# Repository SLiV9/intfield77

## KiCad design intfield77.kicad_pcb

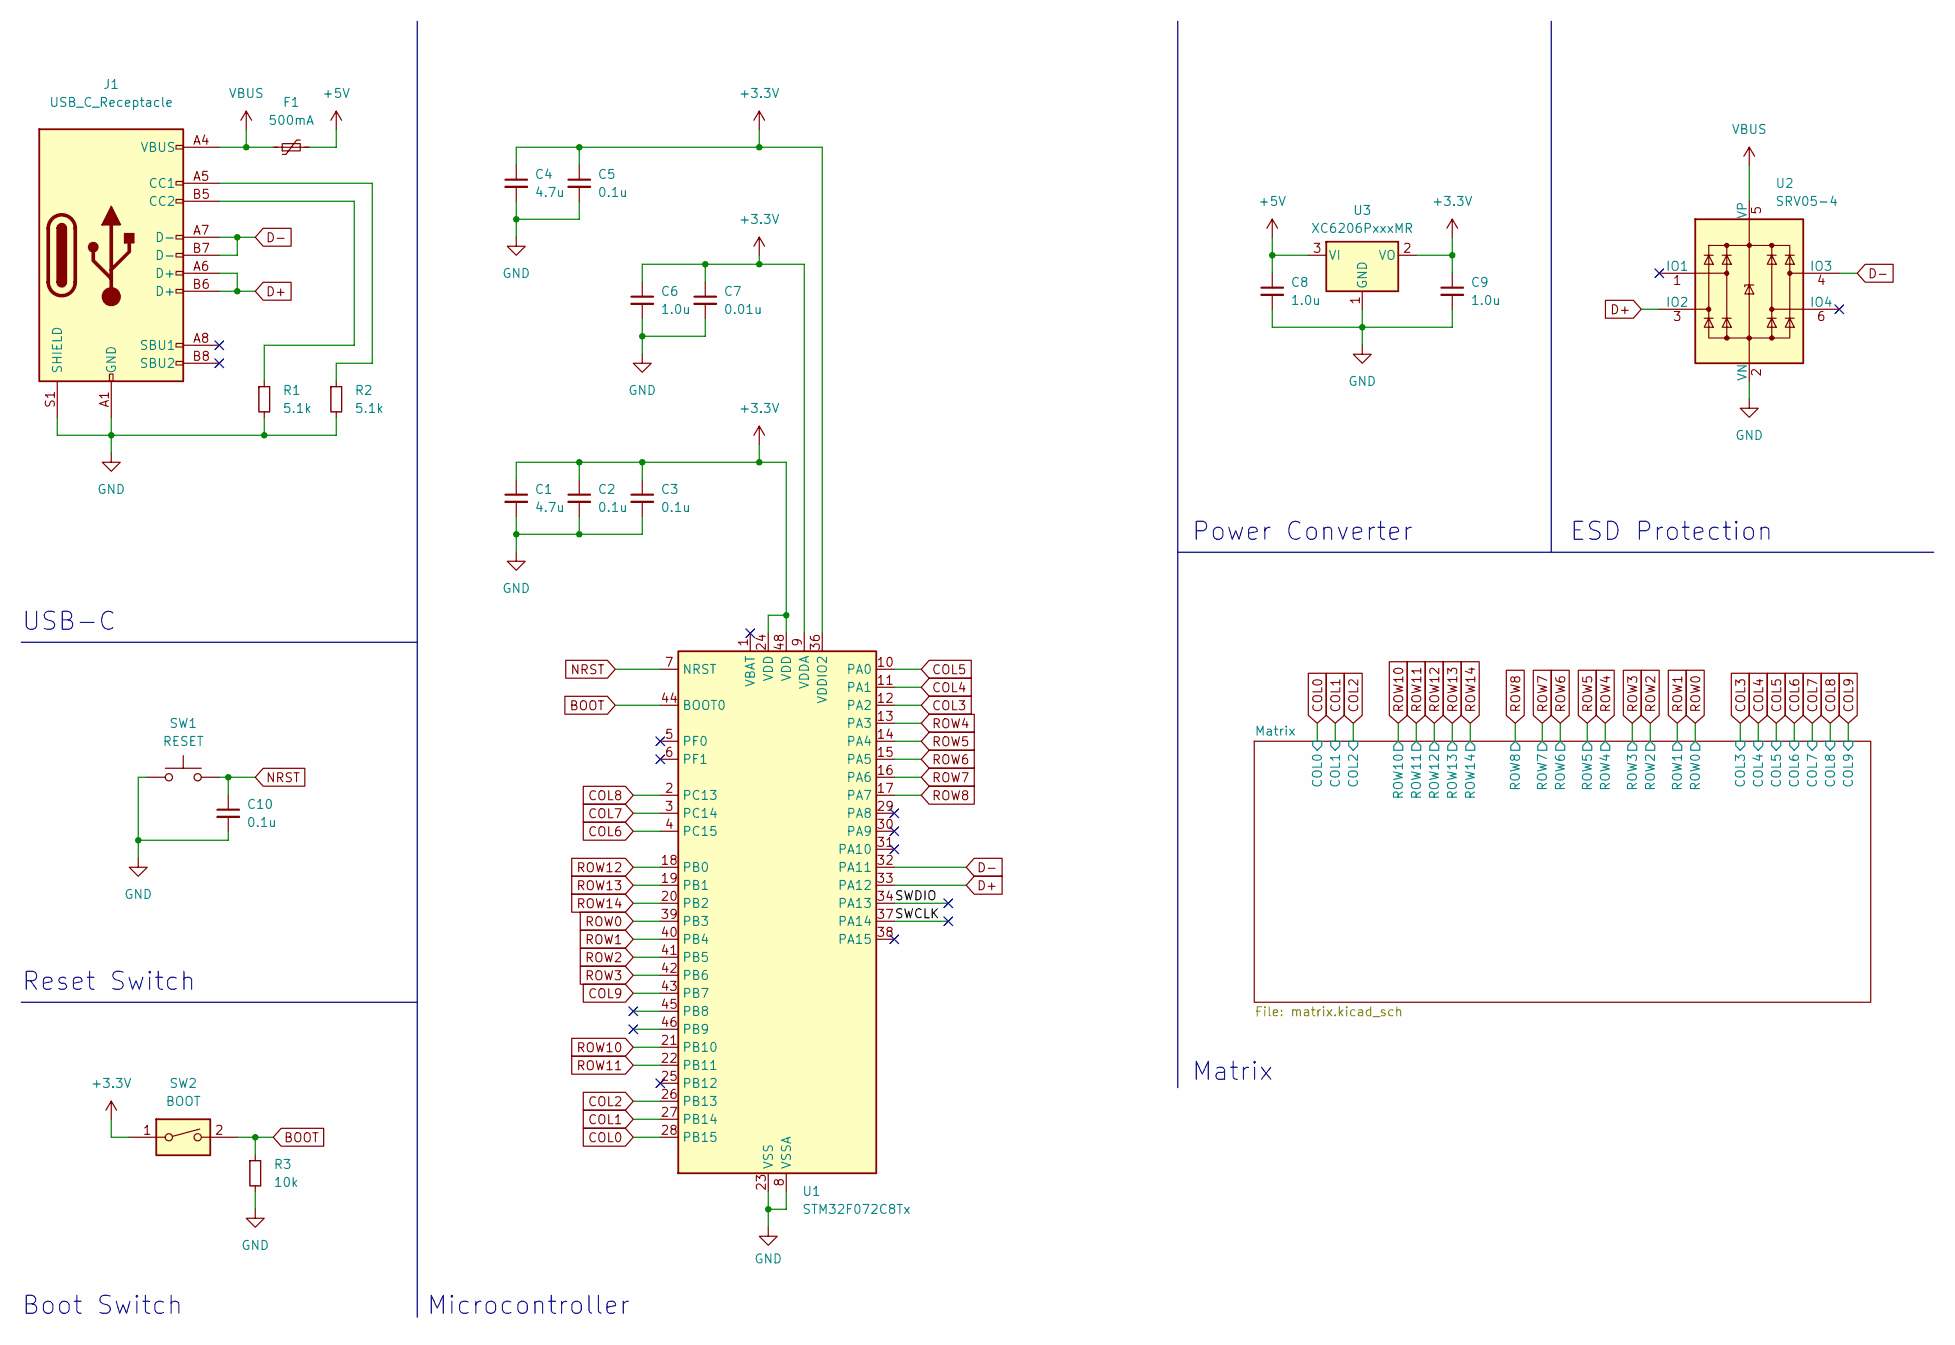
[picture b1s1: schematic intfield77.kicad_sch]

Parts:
C1, C4: 4.7u; C_0805_2012Metric
C2, C3, C5, C10: 0.1u; C_0805_2012Metric
C6, C8, C9: 1.0u; C_0805_2012Metric
C7: 0.01u; C_0805_2012Metric
F1: 500mA; Fuse_1206_3216Metric
J1: USB_C_Receptacle; USB_C_Receptacle_HRO_TYPE-C-31-M-12
R1, R2: 5.1k; R_0805_2012Metric
R3: 10k; R_0805_2012Metric
SW1: RESET; SW_SPST_SKQG_WithStem
SW2: BOOT; SW_DIP_SPSTx01_Slide_9.78x4.72mm_W8.61mm_P2.54mm
U1: STM32F072C8Tx; LQFP-48_7x7mm_P0.5mm
U2: SRV05-4; SOT-23-6-routable
U3: XC6206PxxxMR; SOT-23-3

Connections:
+3.3V: C1.1, C2.1, C3.1, C4.1, C5.1, C6.1, C7.1, C9.1, SW2.1, U1.9 (VDDA), U1.24 (VDD), U1.36 (VDDIO2), U1.48 (VDD), U3.2 (VO)
+5V: C8.1, F1.2, U3.3 (VI)
/SWCLK: U1.37 (PA14)
/SWDIO: U1.34 (PA13)
BOOT: R3.1, SW2.2, U1.44 (BOOT0)
COL0: U1.28 (PB15); also elsewhere on the board
COL1: U1.27 (PB14); also elsewhere on the board
COL2: U1.26 (PB13); also elsewhere on the board
COL3: U1.12 (PA2); also elsewhere on the board
COL4: U1.11 (PA1); also elsewhere on the board
COL5: U1.10 (PA0); also elsewhere on the board
COL6: U1.4 (PC15); also elsewhere on the board
COL7: U1.3 (PC14); also elsewhere on the board
COL8: U1.2 (PC13); also elsewhere on the board
COL9: U1.43 (PB7); also elsewhere on the board
D+: J1.A6 (D+), J1.B6 (D+), U1.33 (PA12), U2.3 (IO2)
D-: J1.A7 (D-), J1.B7 (D-), U1.32 (PA11), U2.4 (IO3)
GND: C1.2, C2.2, C3.2, C4.2, C5.2, C6.2, C7.2, C8.2, C9.2, C10.2, J1.A1 (GND), J1.A12 (GND), J1.B1 (GND), J1.B12 (GND), J1.S1 (SHIELD), R1.2, R2.2, R3.2, SW1.1, U1.8 (VSSA), U1.23 (VSS), U1.35 (VSS), U1.47 (VSS), U2.2 (VN), U3.1 (GND)
NRST: C10.1, SW1.2, U1.7 (NRST)
unnamed: J1.A5 (CC1), R2.1
unnamed: J1.B5 (CC2), R1.1
ROW0: U1.39 (PB3); also elsewhere on the board
ROW1: U1.40 (PB4); also elsewhere on the board
ROW2: U1.41 (PB5); also elsewhere on the board
ROW3: U1.42 (PB6); also elsewhere on the board
ROW4: U1.13 (PA3); also elsewhere on the board
ROW5: U1.14 (PA4); also elsewhere on the board
ROW6: U1.15 (PA5); also elsewhere on the board
ROW7: U1.16 (PA6); also elsewhere on the board
ROW8: U1.17 (PA7); also elsewhere on the board
ROW10: U1.21 (PB10); also elsewhere on the board
ROW11: U1.22 (PB11); also elsewhere on the board
ROW12: U1.18 (PB0); also elsewhere on the board
ROW13: U1.19 (PB1); also elsewhere on the board
ROW14: U1.20 (PB2); also elsewhere on the board
VBUS: F1.1, J1.A4 (VBUS), J1.A9 (VBUS), J1.B4 (VBUS), J1.B9 (VBUS), U2.5 (VP)

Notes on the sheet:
Boot Switch
Power Converter
Matrix
Reset Switch
USB-C
Microcontroller
ESD Protection

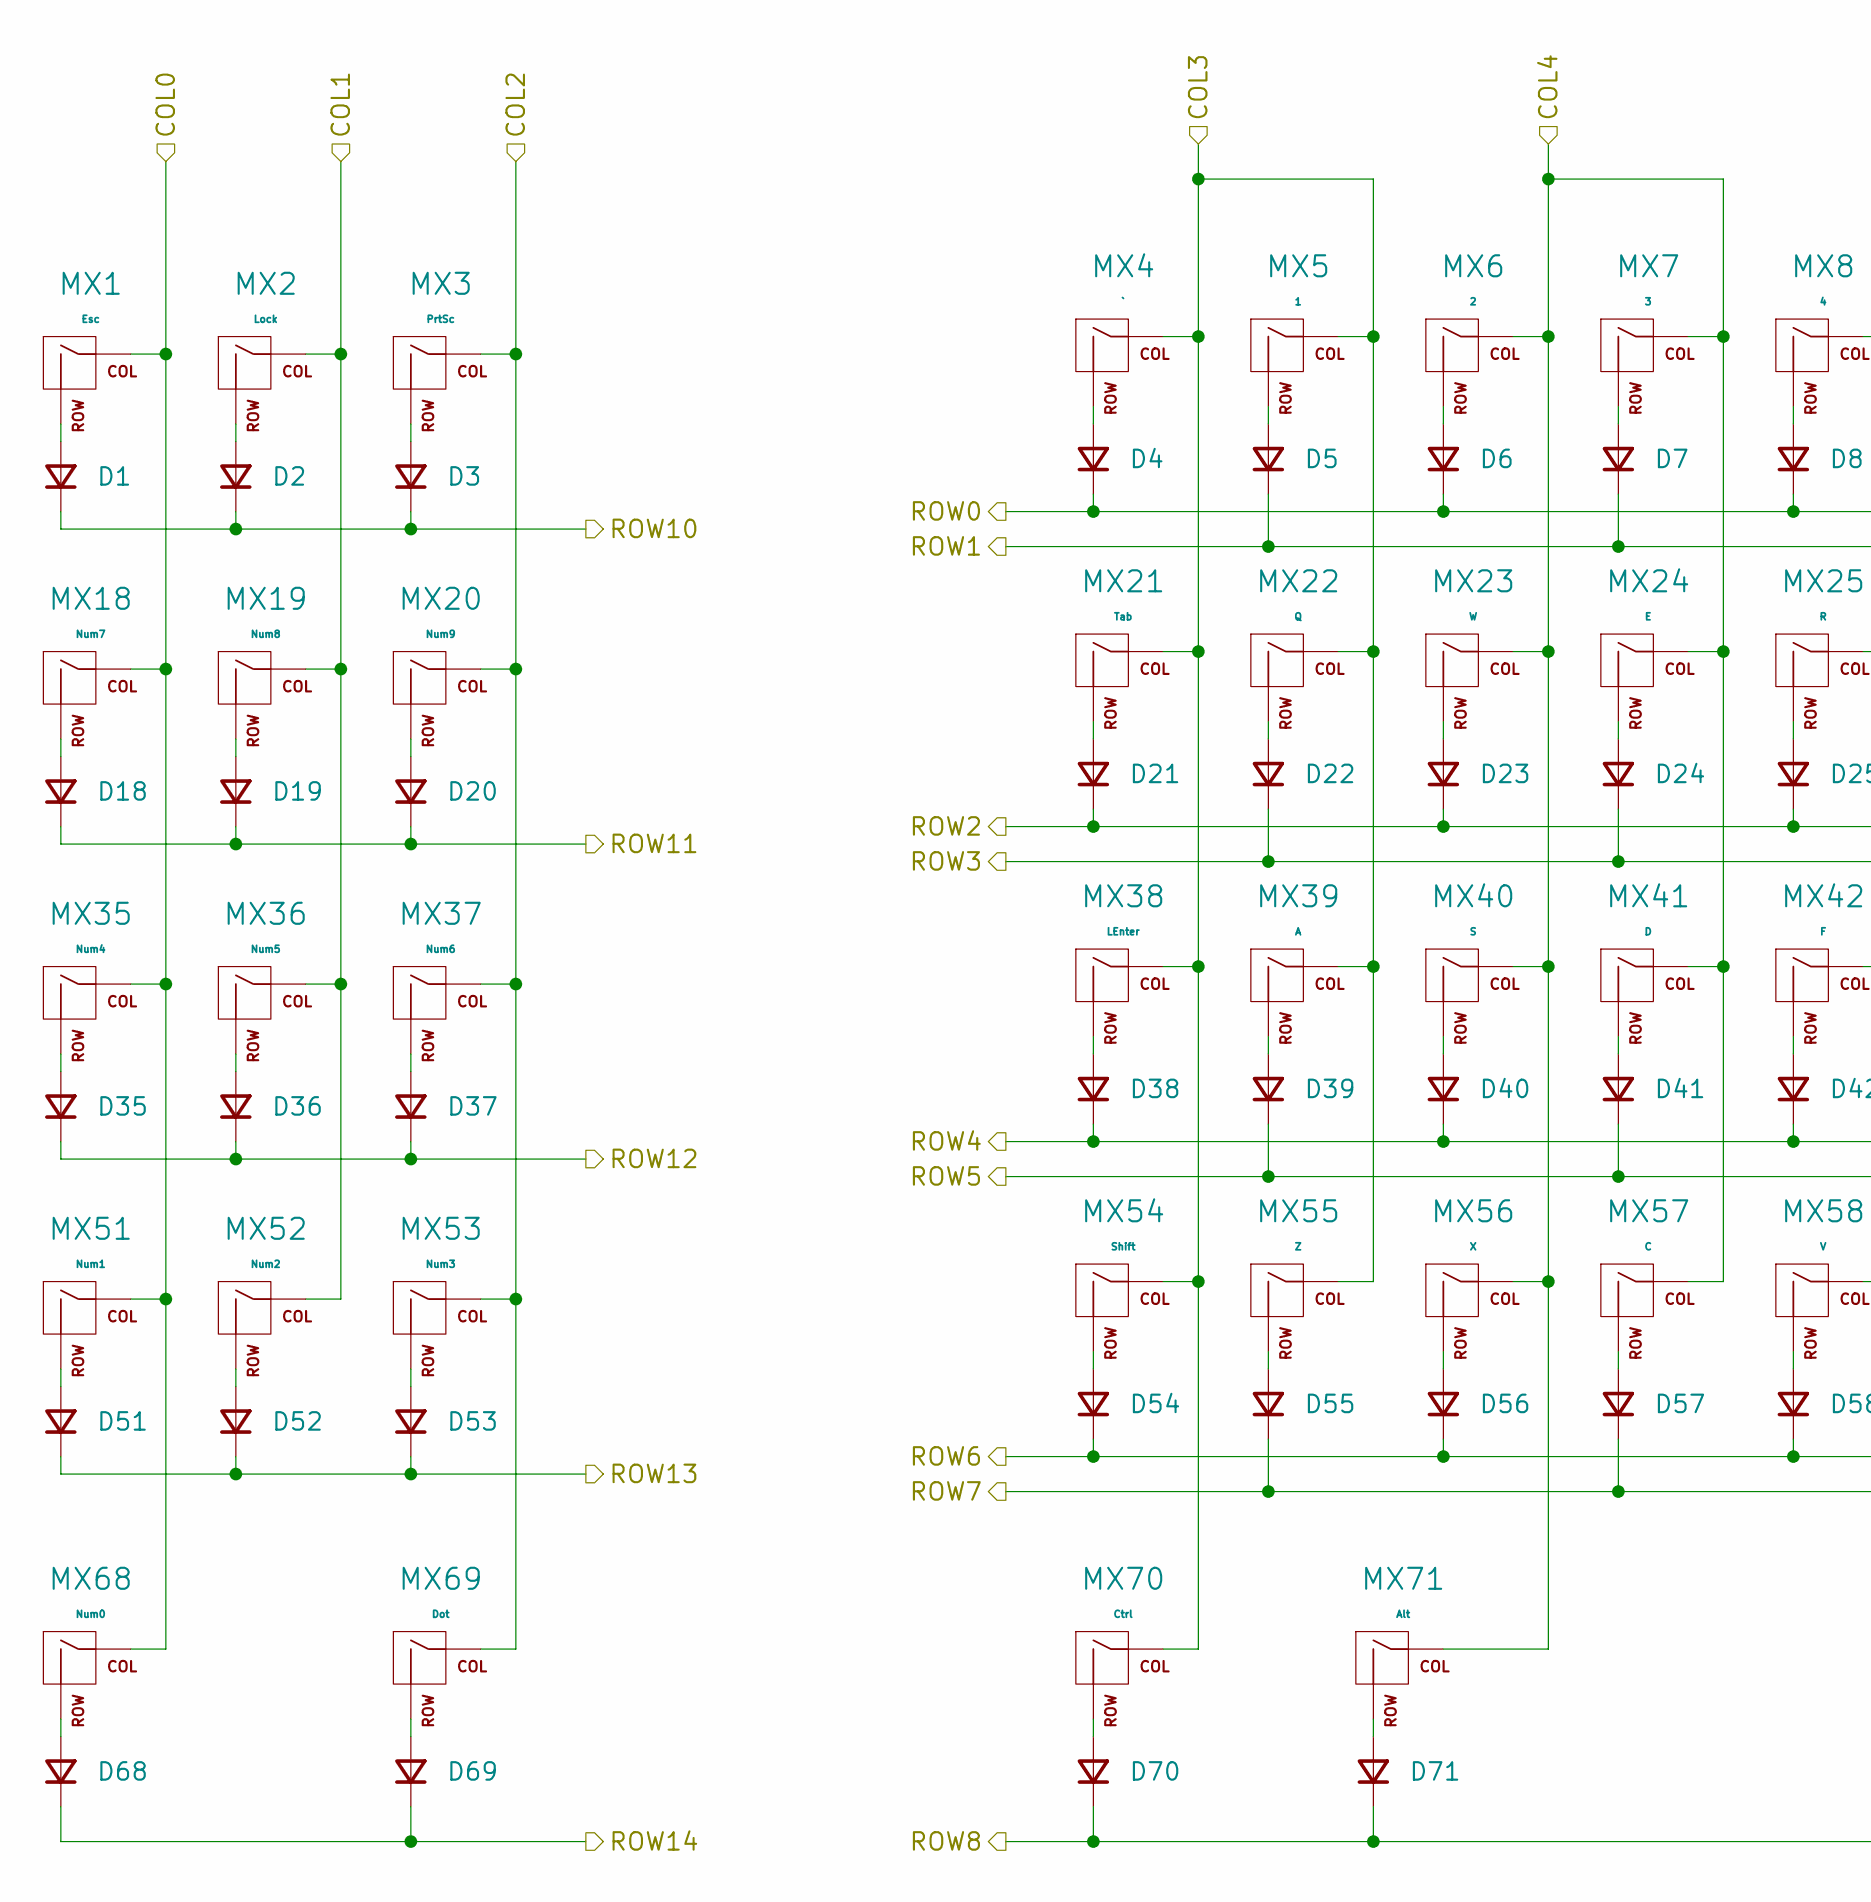
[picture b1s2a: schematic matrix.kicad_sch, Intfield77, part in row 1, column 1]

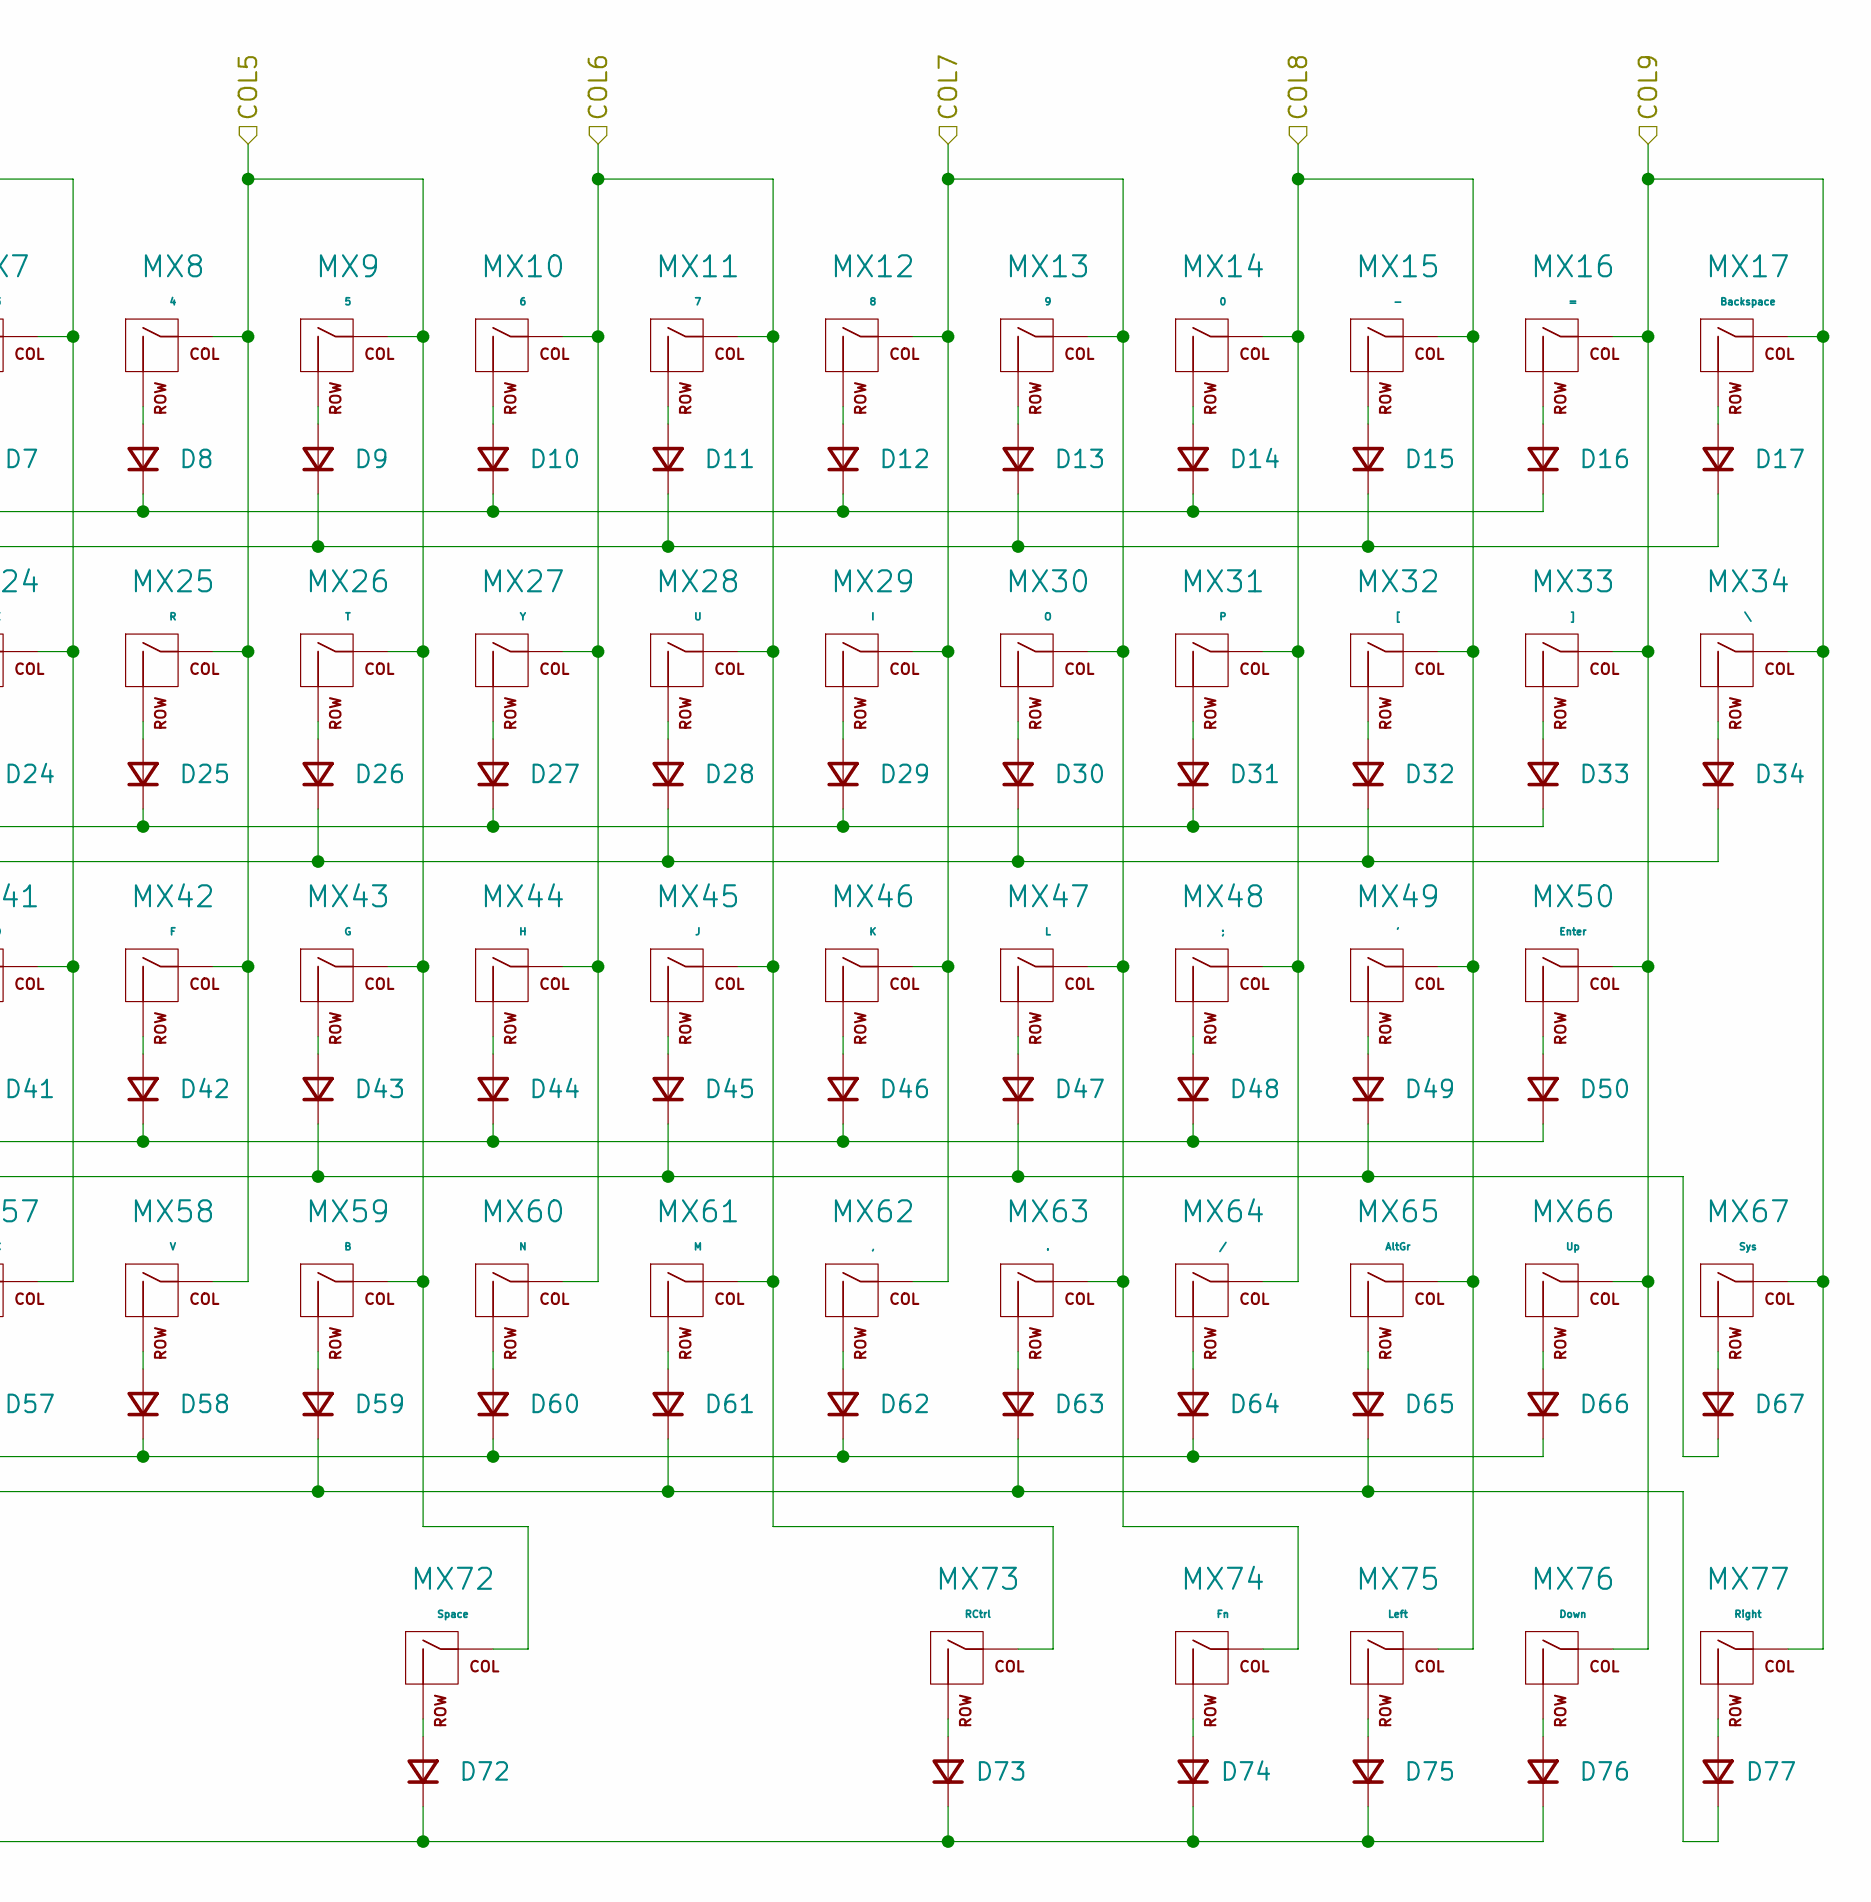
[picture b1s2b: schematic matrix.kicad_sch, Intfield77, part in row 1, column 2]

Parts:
D1, D2, D3, D4, D5, D6, D7, D8, D9, D10, D11, D12, D13, D14, D15, D16, D17, D18, D19, D20, D21, D22, D23, D24, D25, D26, D27, D28, D29, D30, D31, D32, D33, D34, D35, D36, D37, D38, D39, D40, D41, D42, D43, D44, D45, D46, D47, D48, D49, D50, D51, D52, D53, D54, D55, D56, D57, D58, D59, D60, D61, D62, D63, D64, D65, D66, D67, D68, D69, D70, D71, D72, D73, D74, D75, D76, D77: D_SOD-123
MX1: Esc; MXOnly-1U-NoLED
MX2: Lock; MXOnly-1U-NoLED
MX3: PrtSc; MXOnly-1U-NoLED
MX4: `; MXOnly-1U-NoLED
MX5: 1; MXOnly-1U-NoLED
MX6: 2; MXOnly-1U-NoLED
MX7: 3; MXOnly-1U-NoLED
MX8: 4; MXOnly-1U-NoLED
MX9: 5; MXOnly-1U-NoLED
MX10: 6; MXOnly-1U-NoLED
MX11: 7; MXOnly-1U-NoLED
MX12: 8; MXOnly-1U-NoLED
MX13: 9; MXOnly-1U-NoLED
MX14: 0; MXOnly-1U-NoLED
MX15: -; MXOnly-1U-NoLED
MX16: =; MXOnly-1U-NoLED
MX17: Backspace; MXOnly-2U-NoLED
MX18: Num7; MXOnly-1U-NoLED
MX19: Num8; MXOnly-1U-NoLED
MX20: Num9; MXOnly-1U-NoLED
MX21: Tab; MXOnly-1.5U-NoLED
MX22: Q; MXOnly-1U-NoLED
MX23: W; MXOnly-1U-NoLED
MX24: E; MXOnly-1U-NoLED
MX25: R; MXOnly-1U-NoLED
MX26: T; MXOnly-1U-NoLED
MX27: Y; MXOnly-1U-NoLED
MX28: U; MXOnly-1U-NoLED
MX29: I; MXOnly-1U-NoLED
MX30: O; MXOnly-1U-NoLED
MX31: P; MXOnly-1U-NoLED
MX32: [; MXOnly-1U-NoLED
MX33: ]; MXOnly-1U-NoLED
MX34: \; MXOnly-1.5U-NoLED
MX35: Num4; MXOnly-1U-NoLED
MX36: Num5; MXOnly-1U-NoLED
MX37: Num6; MXOnly-1U-NoLED
MX38: LEnter; MXOnly-1.75U-NoLED
MX39: A; MXOnly-1U-NoLED
MX40: S; MXOnly-1U-NoLED
MX41: D; MXOnly-1U-NoLED
MX42: F; MXOnly-1U-NoLED
MX43: G; MXOnly-1U-NoLED
MX44: H; MXOnly-1U-NoLED
MX45: J; MXOnly-1U-NoLED
MX46: K; MXOnly-1U-NoLED
MX47: L; MXOnly-1U-NoLED
MX48: ;; MXOnly-1U-NoLED
MX49: '; MXOnly-1U-NoLED
MX50: Enter; MXOnly-2.25U-NoLED
MX51: Num1; MXOnly-1U-NoLED
MX52: Num2; MXOnly-1U-NoLED
MX53: Num3; MXOnly-1U-NoLED
MX54: Shift; MXOnly-2U-NoLED
MX55: Z; MXOnly-1U-NoLED
MX56: X; MXOnly-1U-NoLED
MX57: C; MXOnly-1U-NoLED
MX58: V; MXOnly-1U-NoLED
MX59: B; MXOnly-1U-NoLED
MX60: N; MXOnly-1U-NoLED
MX61: M; MXOnly-1U-NoLED
MX62: ,; MXOnly-1U-NoLED
MX63: .; MXOnly-1U-NoLED
MX64: /; MXOnly-1U-NoLED
MX65: AltGr; MXOnly-1U-NoLED
MX66: Up; MXOnly-1U-NoLED
MX67: Sys; MXOnly-1U-NoLED
MX68: Num0; MXOnly-2U-NoLED
MX69: Dot; MXOnly-1U-NoLED
MX70: Ctrl; MXOnly-1.25U-NoLED
MX71: Alt; MXOnly-1.25U-NoLED
MX72: Space; MXOnly-7U-NoLED
MX73: RCtrl; MXOnly-1.25U-NoLED
MX74: Fn; MXOnly-1.25U-NoLED
MX75: Left; MXOnly-1U-NoLED
MX76: Down; MXOnly-1U-NoLED
MX77: Right; MXOnly-1U-NoLED

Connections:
COL0: MX1.1 (COL), MX18.1 (COL), MX35.1 (COL), MX51.1 (COL), MX68.1 (COL); also elsewhere on the board
COL1: MX2.1 (COL), MX19.1 (COL), MX36.1 (COL), MX52.1 (COL); also elsewhere on the board
COL2: MX3.1 (COL), MX20.1 (COL), MX37.1 (COL), MX53.1 (COL), MX69.1 (COL); also elsewhere on the board
COL3: MX4.1 (COL), MX5.1 (COL), MX21.1 (COL), MX22.1 (COL), MX38.1 (COL), MX39.1 (COL), MX54.1 (COL), MX55.1 (COL), MX70.1 (COL); also elsewhere on the board
COL4: MX6.1 (COL), MX7.1 (COL), MX23.1 (COL), MX24.1 (COL), MX40.1 (COL), MX41.1 (COL), MX56.1 (COL), MX57.1 (COL), MX71.1 (COL); also elsewhere on the board
COL5: MX8.1 (COL), MX9.1 (COL), MX25.1 (COL), MX26.1 (COL), MX42.1 (COL), MX43.1 (COL), MX58.1 (COL), MX59.1 (COL), MX72.1 (COL); also elsewhere on the board
COL6: MX10.1 (COL), MX11.1 (COL), MX27.1 (COL), MX28.1 (COL), MX44.1 (COL), MX45.1 (COL), MX60.1 (COL), MX61.1 (COL), MX73.1 (COL); also elsewhere on the board
COL7: MX12.1 (COL), MX13.1 (COL), MX29.1 (COL), MX30.1 (COL), MX46.1 (COL), MX47.1 (COL), MX62.1 (COL), MX63.1 (COL), MX74.1 (COL); also elsewhere on the board
COL8: MX14.1 (COL), MX15.1 (COL), MX31.1 (COL), MX32.1 (COL), MX48.1 (COL), MX49.1 (COL), MX64.1 (COL), MX65.1 (COL), MX75.1 (COL); also elsewhere on the board
COL9: MX16.1 (COL), MX17.1 (COL), MX33.1 (COL), MX34.1 (COL), MX50.1 (COL), MX66.1 (COL), MX67.1 (COL), MX76.1 (COL), MX77.1 (COL); also elsewhere on the board
unnamed: D1.2 (A), MX1.2 (ROW)
unnamed: D2.2 (A), MX2.2 (ROW)
unnamed: D3.2 (A), MX3.2 (ROW)
unnamed: D4.2 (A), MX4.2 (ROW)
unnamed: D5.2 (A), MX5.2 (ROW)
unnamed: D6.2 (A), MX6.2 (ROW)
unnamed: D7.2 (A), MX7.2 (ROW)
unnamed: D8.2 (A), MX8.2 (ROW)
unnamed: D9.2 (A), MX9.2 (ROW)
unnamed: D10.2 (A), MX10.2 (ROW)
unnamed: D11.2 (A), MX11.2 (ROW)
unnamed: D12.2 (A), MX12.2 (ROW)
unnamed: D13.2 (A), MX13.2 (ROW)
unnamed: D14.2 (A), MX14.2 (ROW)
unnamed: D15.2 (A), MX15.2 (ROW)
unnamed: D16.2 (A), MX16.2 (ROW)
unnamed: D17.2 (A), MX17.2 (ROW)
unnamed: D18.2 (A), MX18.2 (ROW)
unnamed: D19.2 (A), MX19.2 (ROW)
unnamed: D20.2 (A), MX20.2 (ROW)
unnamed: D21.2 (A), MX21.2 (ROW)
unnamed: D22.2 (A), MX22.2 (ROW)
unnamed: D23.2 (A), MX23.2 (ROW)
unnamed: D24.2 (A), MX24.2 (ROW)
unnamed: D25.2 (A), MX25.2 (ROW)
unnamed: D26.2 (A), MX26.2 (ROW)
unnamed: D27.2 (A), MX27.2 (ROW)
unnamed: D28.2 (A), MX28.2 (ROW)
unnamed: D29.2 (A), MX29.2 (ROW)
unnamed: D30.2 (A), MX30.2 (ROW)
unnamed: D31.2 (A), MX31.2 (ROW)
unnamed: D32.2 (A), MX32.2 (ROW)
unnamed: D33.2 (A), MX33.2 (ROW)
unnamed: D34.2 (A), MX34.2 (ROW)
unnamed: D35.2 (A), MX35.2 (ROW)
unnamed: D36.2 (A), MX36.2 (ROW)
unnamed: D37.2 (A), MX37.2 (ROW)
unnamed: D38.2 (A), MX38.2 (ROW)
unnamed: D39.2 (A), MX39.2 (ROW)
unnamed: D40.2 (A), MX40.2 (ROW)
unnamed: D41.2 (A), MX41.2 (ROW)
unnamed: D42.2 (A), MX42.2 (ROW)
unnamed: D43.2 (A), MX43.2 (ROW)
unnamed: D44.2 (A), MX44.2 (ROW)
unnamed: D45.2 (A), MX45.2 (ROW)
unnamed: D46.2 (A), MX46.2 (ROW)
unnamed: D47.2 (A), MX47.2 (ROW)
unnamed: D48.2 (A), MX48.2 (ROW)
unnamed: D49.2 (A), MX49.2 (ROW)
unnamed: D50.2 (A), MX50.2 (ROW)
unnamed: D51.2 (A), MX51.2 (ROW)
unnamed: D52.2 (A), MX52.2 (ROW)
unnamed: D53.2 (A), MX53.2 (ROW)
unnamed: D54.2 (A), MX54.2 (ROW)
unnamed: D55.2 (A), MX55.2 (ROW)
unnamed: D56.2 (A), MX56.2 (ROW)
unnamed: D57.2 (A), MX57.2 (ROW)
unnamed: D58.2 (A), MX58.2 (ROW)
unnamed: D59.2 (A), MX59.2 (ROW)
unnamed: D60.2 (A), MX60.2 (ROW)
unnamed: D61.2 (A), MX61.2 (ROW)
unnamed: D62.2 (A), MX62.2 (ROW)
unnamed: D63.2 (A), MX63.2 (ROW)
unnamed: D64.2 (A), MX64.2 (ROW)
unnamed: D65.2 (A), MX65.2 (ROW)
unnamed: D66.2 (A), MX66.2 (ROW)
unnamed: D67.2 (A), MX67.2 (ROW)
unnamed: D68.2 (A), MX68.2 (ROW)
unnamed: D69.2 (A), MX69.2 (ROW)
unnamed: D70.2 (A), MX70.2 (ROW)
unnamed: D71.2 (A), MX71.2 (ROW)
unnamed: D72.2 (A), MX72.2 (ROW)
unnamed: D73.2 (A), MX73.2 (ROW)
unnamed: D74.2 (A), MX74.2 (ROW)
unnamed: D75.2 (A), MX75.2 (ROW)
unnamed: D76.2 (A), MX76.2 (ROW)
unnamed: D77.2 (A), MX77.2 (ROW)
ROW0: D4.1 (K), D6.1 (K), D8.1 (K), D10.1 (K), D12.1 (K), D14.1 (K), D16.1 (K); also elsewhere on the board
ROW1: D5.1 (K), D7.1 (K), D9.1 (K), D11.1 (K), D13.1 (K), D15.1 (K), D17.1 (K); also elsewhere on the board
ROW2: D21.1 (K), D23.1 (K), D25.1 (K), D27.1 (K), D29.1 (K), D31.1 (K), D33.1 (K); also elsewhere on the board
ROW3: D22.1 (K), D24.1 (K), D26.1 (K), D28.1 (K), D30.1 (K), D32.1 (K), D34.1 (K); also elsewhere on the board
ROW4: D38.1 (K), D40.1 (K), D42.1 (K), D44.1 (K), D46.1 (K), D48.1 (K), D50.1 (K); also elsewhere on the board
ROW5: D39.1 (K), D41.1 (K), D43.1 (K), D45.1 (K), D47.1 (K), D49.1 (K), D67.1 (K); also elsewhere on the board
ROW6: D54.1 (K), D56.1 (K), D58.1 (K), D60.1 (K), D62.1 (K), D64.1 (K), D66.1 (K); also elsewhere on the board
ROW7: D55.1 (K), D57.1 (K), D59.1 (K), D61.1 (K), D63.1 (K), D65.1 (K), D77.1 (K); also elsewhere on the board
ROW8: D70.1 (K), D71.1 (K), D72.1 (K), D73.1 (K), D74.1 (K), D75.1 (K), D76.1 (K); also elsewhere on the board
ROW10: D1.1 (K), D2.1 (K), D3.1 (K); also elsewhere on the board
ROW11: D18.1 (K), D19.1 (K), D20.1 (K); also elsewhere on the board
ROW12: D35.1 (K), D36.1 (K), D37.1 (K); also elsewhere on the board
ROW13: D51.1 (K), D52.1 (K), D53.1 (K); also elsewhere on the board
ROW14: D68.1 (K), D69.1 (K); also elsewhere on the board

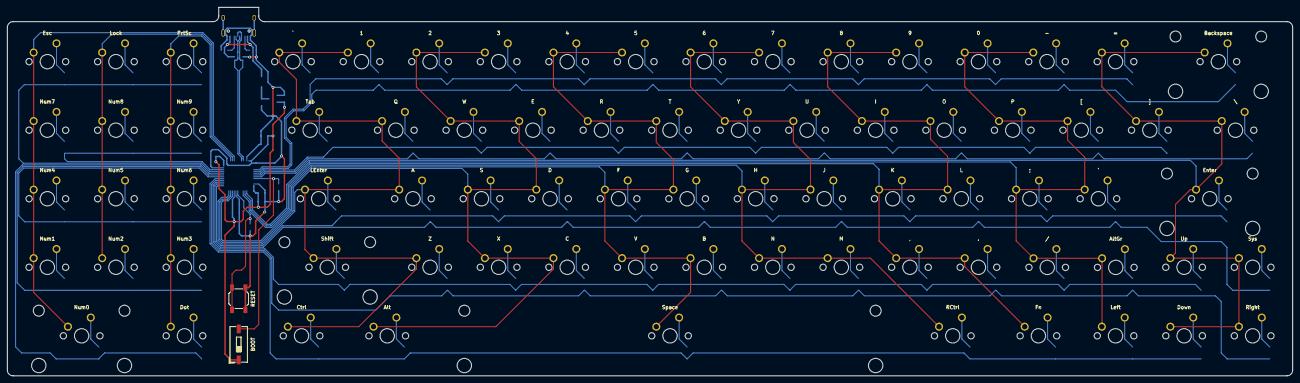
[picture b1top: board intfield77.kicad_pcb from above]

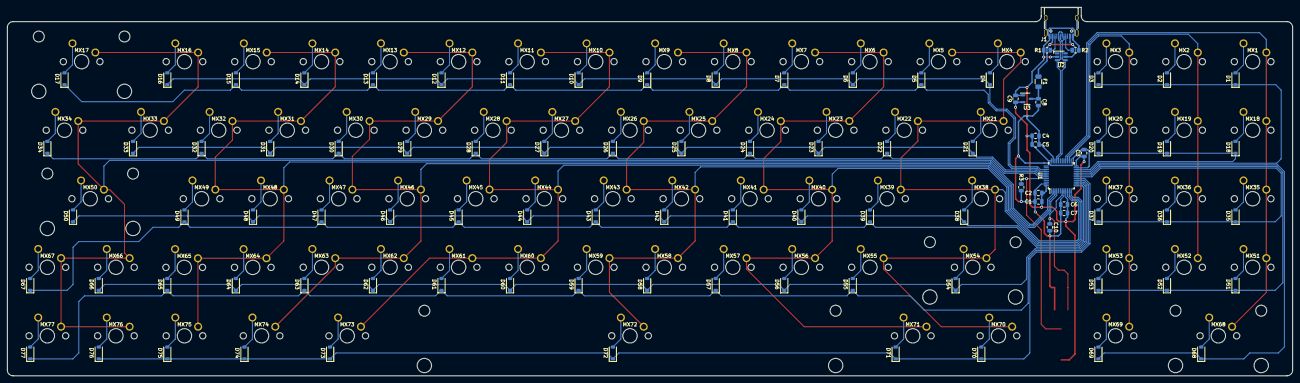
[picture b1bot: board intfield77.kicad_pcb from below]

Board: 2 copper layers, 357.2 x 102.4 mm, 174 parts (95 on the bottom side), 111 nets.

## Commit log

2023-08-12 Empty project.
2023-08-12 Libraries
2023-08-13 Started on MCU and USB-C connector.
2023-08-13 First version of schematic, including duplex matrix.
2023-08-13 Trying to connect the matrix sheet with the main sheet.
2023-08-13 Matrix is connected to rest of schematic.
2023-08-15 Assigned footprints, key labels and placed key switches on PCB. Removed SWD component.
2023-08-17 Placed diodes and roughly placed other PCB components.
2023-08-18 Shuffled MCU pins and realigned schema to 50 mils, but USB connector is not connected.
2023-08-18 Changed USB-C and reset button symbols and footprints, still problems.
2023-08-18 Fixed it, I think.
2023-08-20 First routing of the PCB except the matrices.
2023-08-20 Routing the matrices, but I might redo the pin assignments again.
2023-08-20 Reassigned pins and complete routing.
2023-08-20 Changed the silkscreen for the MX footprints.
